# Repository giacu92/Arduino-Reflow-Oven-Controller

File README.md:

# GFE-Reflow-Oven-Controller v2
This repo contains all the files of my Arduino Zero (samd21) based Reflow Oven PID Controller for reflow smd soldering.

* Author: Giacomo Mammarella
* email: giacu92@gmail.com,

[Check the live version!](https://a360.co/3yNSDE0)

# For Arduino Nano (V1.1) refer to appropriate branch --> [v1.1](https://github.com/giacu92/Arduino-Reflow-Oven-Controller/tree/v1.1)

# File list:
* [Arduino files](https://github.com/giacu92/Reflow-Oven-Controller/tree/master/GFE_Reflow_Oven_Controller): The Arduino files source folder.
* [Processing file](https://github.com/giacu92/Reflow-Oven-Controller/tree/master/Processing/Reflow_oven_serial_controller): The Processing files source folder.
* [Prova.brd](https://github.com/giacu92/GFE-Reflow-Oven-Controller/blob/master/Prova.brd): Cadsoft Eagle 6.5 .brd file of my Reflow Oven Controller. 
* [Prova.sch](https://github.com/giacu92/GFE-Reflow-Oven-Controller/blob/master/Prova.sch): Cadsoft Eagle 6.5 .sch file of my Reflow Oven Controller.

# Mounting the board:
Get a fully assembled board [here](http://giacu92.bigcartel.com/product/reflow-oven-controller-board-v1-1) or etch it yourself. -- available soon

A newer version of the pcb featuring two thermocouple interface, +12V fan output (for cooling) is under development. It will fit the 16x2 LCD screen and mounts underneath it. Here's a sample rendering. Also a new pid autotuner function and MicroSD card interface for saving custom profiles are getting implemented.

This project is under continuous update (May 2022). Contact me for anything :)

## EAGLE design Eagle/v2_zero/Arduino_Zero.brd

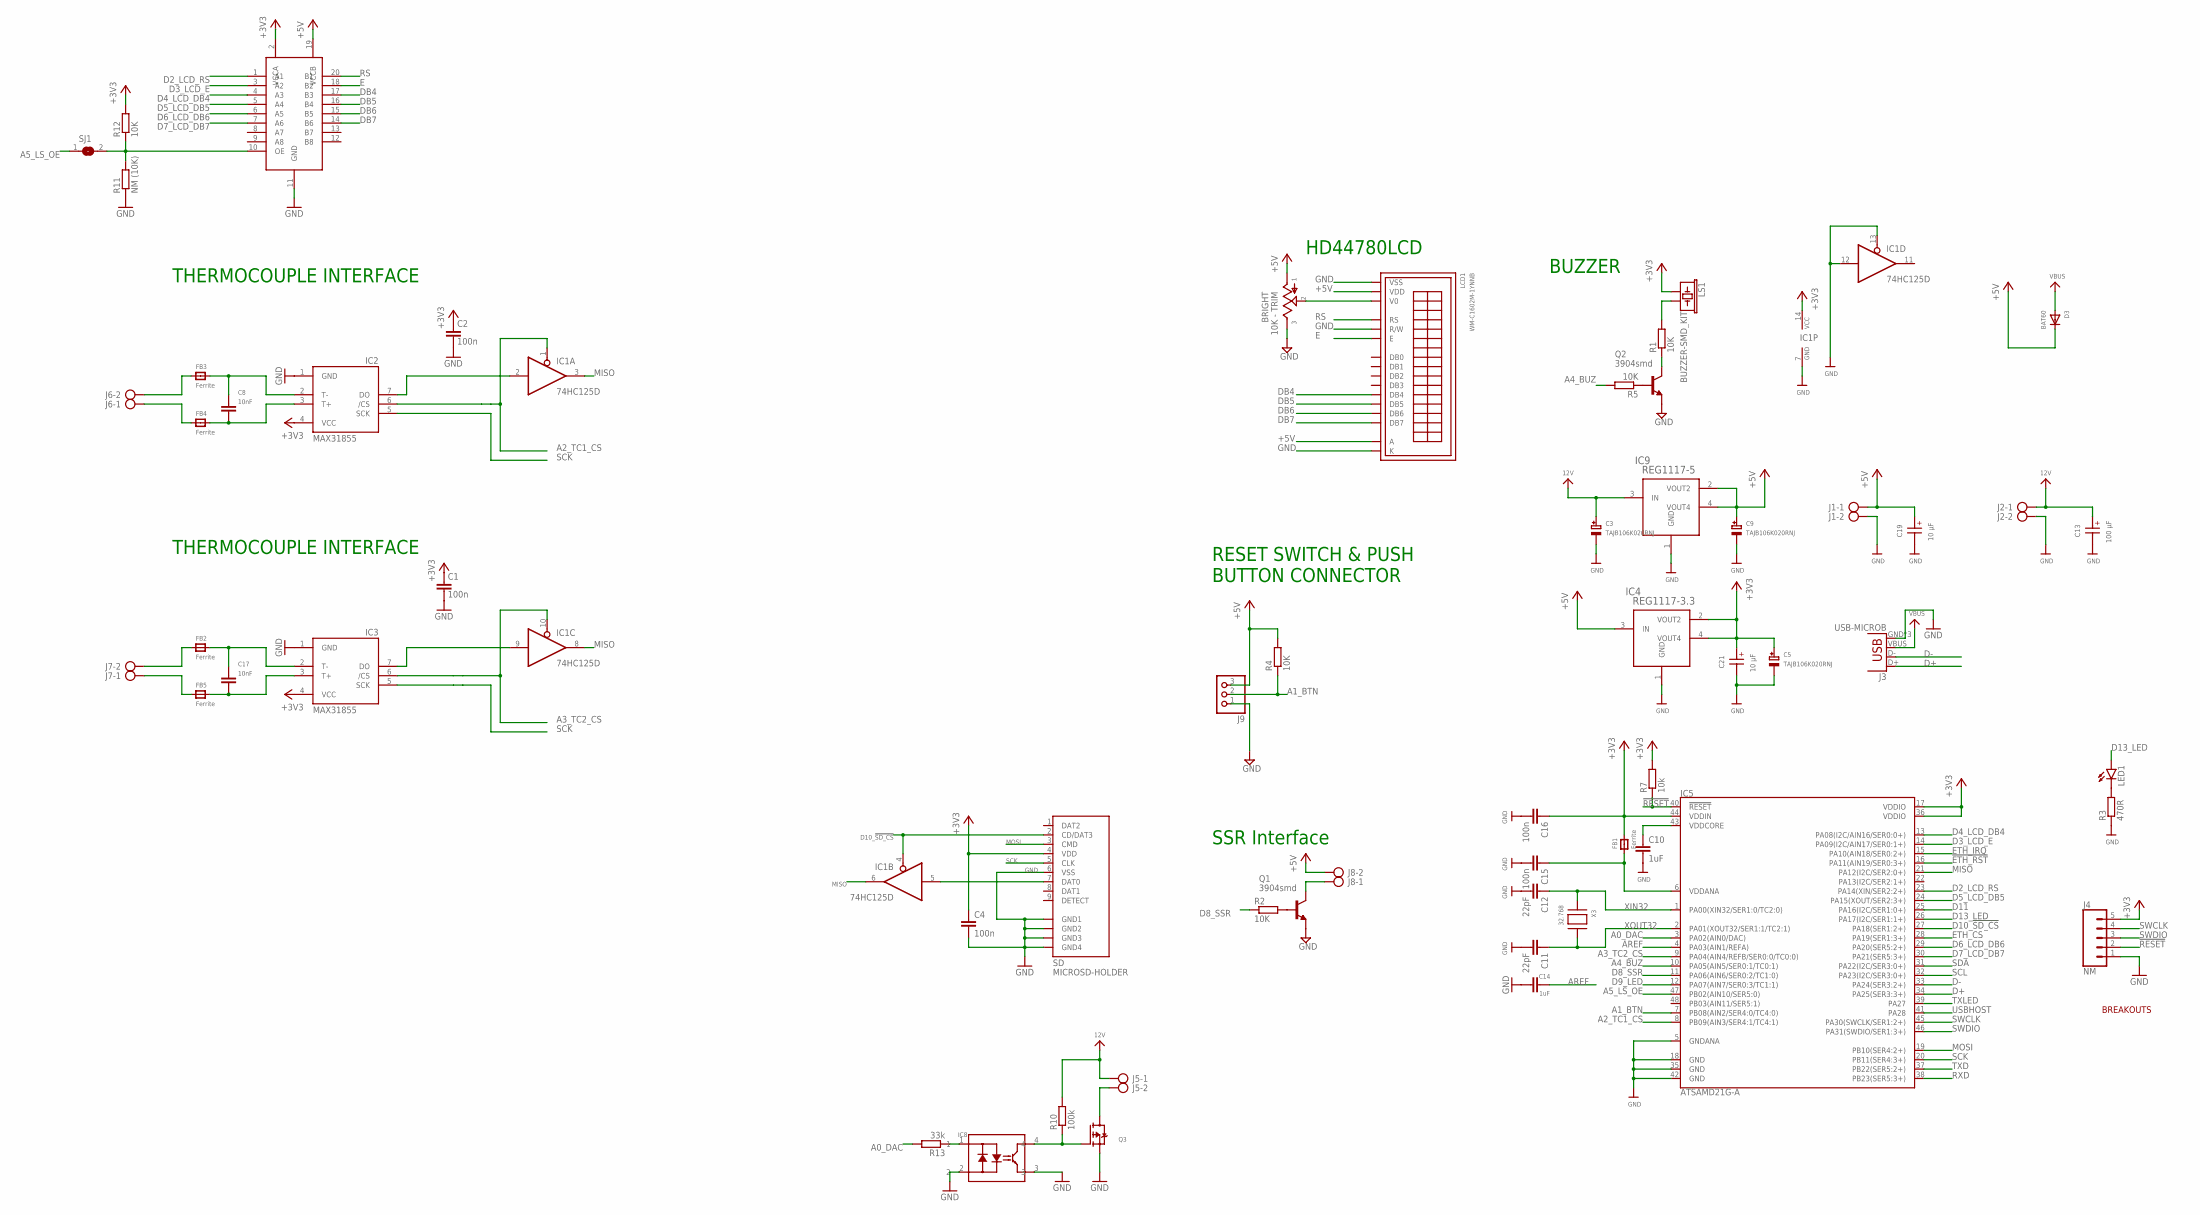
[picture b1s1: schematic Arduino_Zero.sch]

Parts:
BRIGHT: 10K - TRIM; B25P
C1, C2, C4, C15, C16: 100n; C0603K
C3, C5, C9: TAJB106K020RNJ; CAPMP3528X210N
C8, C17: 10nF; C0603K
C10, C14: 1uF; C0603K
C11, C12: 22pF; C0603K
C13: 100 µF; WCAP-ASLI_6.3X7.7(DXL)
C19, C21: 10 µF; WCAP-ASLI_4X5.5(DXL)
D3: BAT60; SOD323
FB1, FB2, FB3, FB4, FB5: Ferrite; BEADC3216X100N
IC1: 74HC125D; SO14
IC2, IC3: MAX31855; SO08
IC4: REG1117-3.3; DCY0004A_N
IC5: ATSAMD21G-A; TQFP-48
IC7: TXS0108E; TSSOP20
IC8: TLP283; SO4_TOS
IC9: REG1117-5; DCY0004A_N
J1, J2, J5, J6, J7, J8: AK500/2ASD; AK500/2
J3: USB-MICROB
J4: NM; 1X05_1.27MM
J9: PINHD-1X3; 1X03
LCD1: WM-C1602M-1YNNB; LCD_2
LED1: LEDCHIPLED_0805; CHIPLED_0805
LS1: BUZZER-SMD_KIT; BUZZER-CCV-KIT
Q1, Q2: 3904smd; SOT23-BEC
Q3: MOSFET-PWIDE; SOT23-WIDE
R1, R2, R4, R5, R12: 10K; R0603
R3: 470R; R0603
R7: 10k; R0603
R10: 100k; R0603
R11: NM (10K); R0603
R13: 33k; R0603
SD: MICROSD-HOLDER; MICROSD-HOLDER-ALIEX
SJ1: SJ
X3: 32.768; XTAL3215

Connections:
12V: C3.1 (+), C13.1 (+), IC9.3 (IN), J2.1, J5.1, R10.2
!ETH_RST: IC5.16 (PA11(AIN19/SER0:3+))
!RESET: IC5.40 (!RESET!), J4.2, R7.1
+3V3: C1.1, C2.1, C4.1, C5.1 (+), C16.1, C21.1 (+), FB1.2, IC1.14 (VCC), IC2.4 (VCC), IC3.4 (VCC), IC4.2 (VOUT2), IC4.4 (VOUT4), IC5.17 (VDDIO), IC5.36 (VDDIO), IC5.44 (VDDIN), IC7.2 (VCCA), J4.5, LS1.+ (1), R7.2, R12.2, SD.4 (VDD)
+5V: BRIGHT.1, C9.1 (+), C19.1 (+), D3.1 (C), IC4.3 (IN), IC7.19 (VCCB), IC9.2 (VOUT2), IC9.4 (VOUT4), J1.1, J8.2, J9.3, LCD1.2 (VDD), LCD1.15 (A), R4.2
A0_DAC: IC5.3 (PA02(AIN0/DAC)), R13.2
A1_BTN: IC5.7 (PB08(AIN2/SER4:0/TC4:0)), J9.2, R4.1
A2_TC1_CS: IC1.1 (OE), IC2.6 (/CS), IC5.8 (PB09(AIN3/SER4:1/TC4:1))
A3_TC2_CS: IC1.10 (OE), IC3.6 (/CS), IC5.9 (PA04(AIN4/REFB/SER0:0/TC0:0))
A4_BUZ: IC5.10 (PA05(AIN5/SER0:1/TC0:1)), R5.2
A5_LS_OE: IC5.47 (PB02(AIN10/SER5:0)), SJ1.1
AREF: C14.1, IC5.4 (PA03(AIN1/REFA))
D2_LCD_RS: IC5.23 (PA14(XIN/SER2:2+)), IC7.1 (A1)
D3_LCD_E: IC5.14 (PA09(I2C/AIN17/SER0:1+)), IC7.3 (A2)
D4_LCD_DB4: IC5.13 (PA08(I2C/AIN16/SER0:0+)), IC7.4 (A3)
D5_LCD_DB5: IC5.24 (PA15(XOUT/SER2:3+)), IC7.5 (A4)
D6_LCD_DB6: IC5.29 (PA20(SER5:2+)), IC7.6 (A5)
D7_LCD_DB7: IC5.30 (PA21(SER5:3+)), IC7.7 (A6)
D8_SSR: IC5.11 (PA06(AIN6/SER0:2/TC1:0)), R2.1
D9_LED: IC5.12 (PA07(AIN7/SER0:3/TC1:1))
D10_!SD_CS: IC1.4 (OE), IC5.27 (PA18(SER1:2+)), SD.2 (CD/DAT3)
D11: IC5.25 (PA16(I2C/SER1:0+))
D13_LED: IC5.26 (PA17(I2C/SER1:1+)), LED1.A
D+: IC5.34 (PA25(SER3:3+)), J3.D+
D-: IC5.33 (PA24(SER3:2+)), J3.D-
DB4: IC7.17 (B3), LCD1.11 (DB4)
DB5: IC7.16 (B4), LCD1.12 (DB5)
DB6: IC7.15 (B5), LCD1.13 (DB6)
DB7: IC7.14 (B6), LCD1.14 (DB7)
E: IC7.18 (B2), LCD1.6 (E)
ETH_CS: IC5.28 (PA19(SER1:3+))
ETH_IRQ: IC5.15 (PA10(AIN18/SER0:2+))
GND: BRIGHT.3, C1.2, C2.2, C3.2 (-), C4.2, C5.2 (-), C9.2 (-), C10.2, C11.2, C12.2, C13.2 (-), C14.2, C15.2, C16.2, C19.2 (-), C21.2 (-), IC1.7 (GND), IC1.12 (I), IC1.13 (OE), IC2.1 (GND), IC3.1 (GND), IC4.1 (GND), IC5.5 (GNDANA), IC5.18 (GND), IC5.35 (GND), IC5.42 (GND), IC7.11 (GND), IC8.2, IC8.3, IC9.1 (GND), J1.2, J2.2, J3.GND, J3.MT1 (GND), J3.MT2 (GND), J4.1, J9.1, LCD1.1 (VSS), LCD1.5 (R/W), LCD1.16 (K), Q1.E, Q2.E, Q3.2 (S), R3.1, R11.1, SD.6 (VSS), SD.P$1 (GND1), SD.P$2 (GND2), SD.P$3 (GND3), SD.P$4 (GND4)
MISO: IC1.3 (O), IC1.6 (O), IC1.8 (O), IC5.21 (PA12(I2C/SER2:0+))
MOSI: IC5.19 (PB10(SER4:2+)), SD.3 (CMD)
unnamed: Q2.B, R5.1
unnamed: J8.1, Q1.C
unnamed: Q1.B, R2.2
unnamed: LS1.- (2), R1.2
unnamed: BRIGHT.2, LCD1.3 (V0)
unnamed: LED1.C, R3.2
unnamed: IC1.2 (I), IC2.7 (DO)
unnamed: IC1.5 (I), SD.7 (DAT0)
unnamed: J5.2, Q3.3 (D)
unnamed: IC7.10 (OE), R11.2, R12.1, SJ1.2
unnamed: FB2.1, J7.2
unnamed: IC8.1, R13.1
unnamed: C17.1, FB2.2, IC3.2 (T-)
unnamed: IC8.4, Q3.1 (G), R10.1
unnamed: FB5.1, J7.1
unnamed: C17.2, FB5.2, IC3.3 (T+)
unnamed: Q2.C, R1.1
unnamed: IC1.9 (I), IC3.7 (DO)
unnamed: FB3.1, J6.2
unnamed: C8.1, FB3.2, IC2.2 (T-)
unnamed: FB4.1, J6.1
unnamed: C8.2, FB4.2, IC2.3 (T+)
unnamed: C15.1, FB1.1, IC5.6 (VDDANA)
unnamed: C10.1, IC5.43 (VDDCORE)
RS: IC7.20 (B1), LCD1.4 (RS)
RXD: IC5.38 (PB23(SER5:3+))
SCK: IC2.5 (SCK), IC3.5 (SCK), IC5.20 (PB11(SER4:3+)), SD.5 (CLK)
SCL: IC5.32 (PA23(I2C/SER3:0+))
SDA: IC5.31 (PA22(I2C/SER3:0+))
SWCLK: IC5.45 (PA30(SWCLK/SER1:2+)), J4.4
SWDIO: IC5.46 (PA31(SWDIO/SER1:3+)), J4.3
TXD: IC5.37 (PB22(SER5:2+))
TXLED: IC5.39 (PA27)
USBHOST: IC5.41 (PA28)
VBUS: D3.2 (A), J3.VBUS
XIN32: C12.1, IC5.1 (PA00(XIN32/SER1:0/TC2:0)), X3.P$1
XOUT32: C11.1, IC5.2 (PA01(XOUT32/SER1:1/TC2:1)), X3.P$2

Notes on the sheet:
SSR Interface
BUZZER
HD44780LCD
RESET SWITCH & PUSH BUTTON CONNECTOR
THERMOCOUPLE INTERFACE
BREAKOUTS

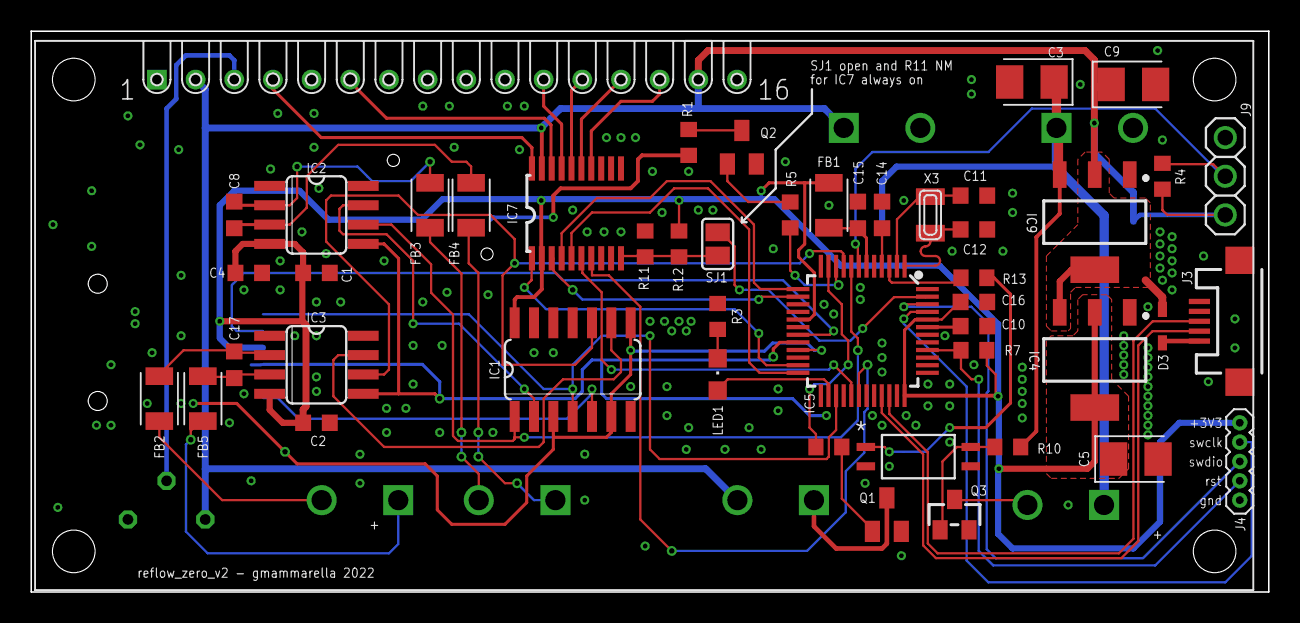
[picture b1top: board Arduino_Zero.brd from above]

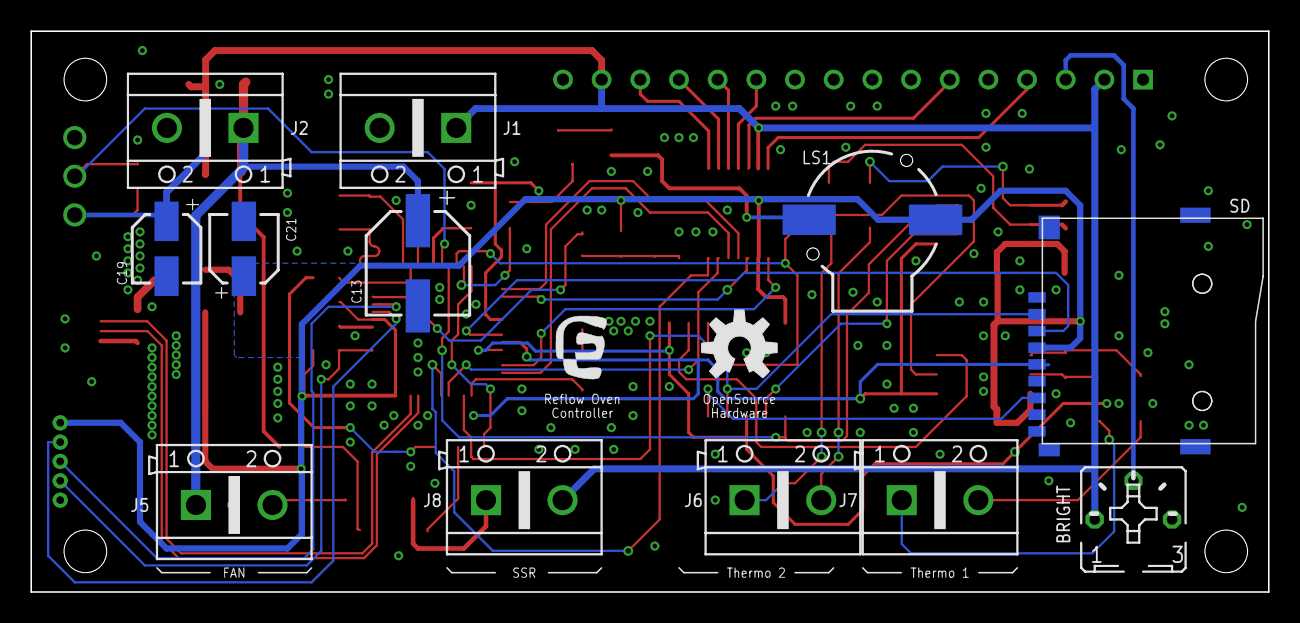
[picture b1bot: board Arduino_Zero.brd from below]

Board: 2 copper layers, 81.3 x 36.8 mm, 62 parts (14 on the bottom side), 61 nets.

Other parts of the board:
U$1: LOGO_PICCOLO
U$2: OSHW-LOGO-M

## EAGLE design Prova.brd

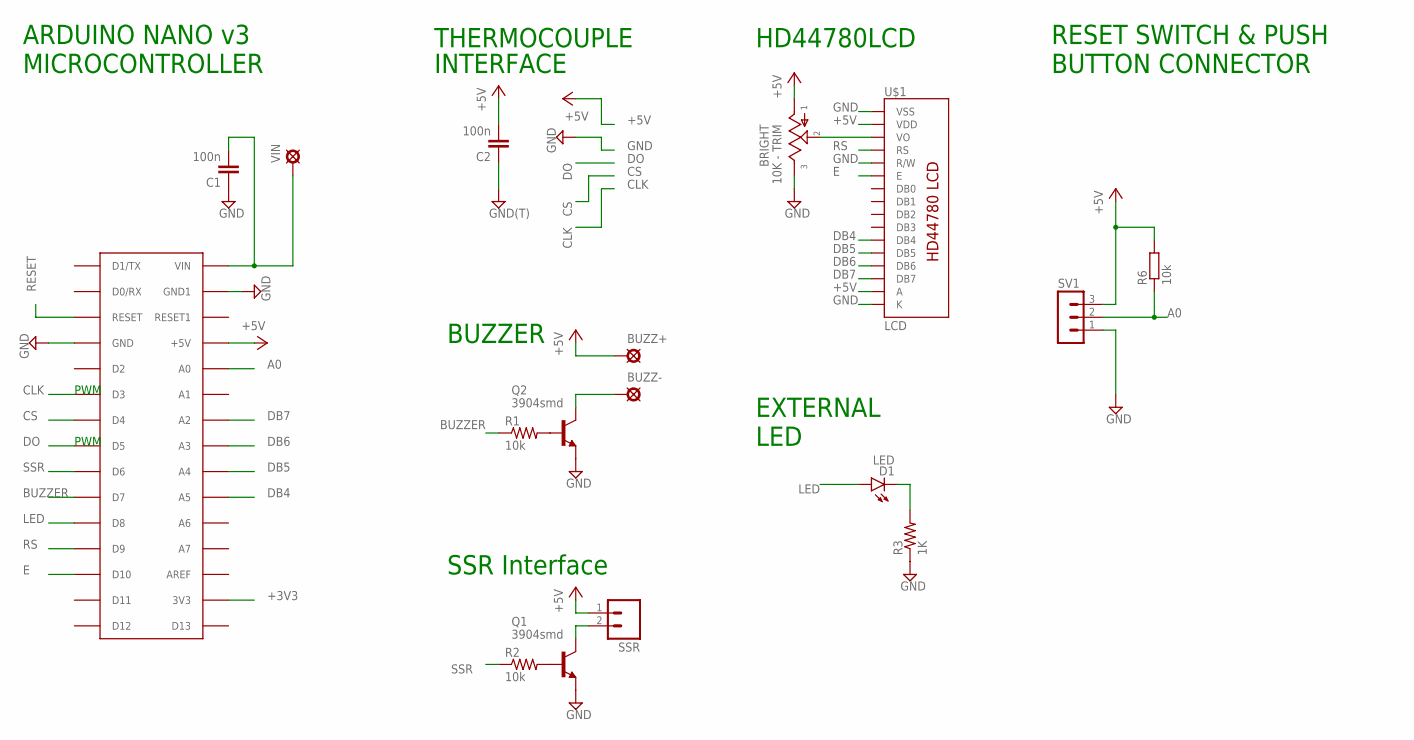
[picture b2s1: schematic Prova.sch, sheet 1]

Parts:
ARDUINO: Arduino Nano v3.0; PDIP-32
BRIGHT: 10K - TRIM; B25P
BUZZ+: PAD; SQUARE
BUZZ-: PAD8; OCTOGON
C1, C2: 100n; 0805
D1: LED; LED3MM
GND8: GND(T); SQUARE
Q1, Q2: 3904smd; SOT23-BEC
R1, R2: 10k; R0207/3
R3: 1K; R0207/3
R6: 10k; M0805
SSR: M023.5MM; SCREWTERMINAL-3.5MM-2
SV1: MA03-1
U$1: LCD; LCD-16X2-PIN
VIN: PAD; SQUARE

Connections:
+3V3: ARDUINO.3V3; also elsewhere on the board
+5V: ARDUINO.+5V, BRIGHT.1, BUZZ+.1, C2.2, R6.2, SSR.1, SV1.3, U$1.2 (VDD), U$1.15 (A)
A0: ARDUINO.A0, R6.1, SV1.2
BUZZER: ARDUINO.D7, R1.1
CLK: ARDUINO.D3; also elsewhere on the board
CS: ARDUINO.D4; also elsewhere on the board
DB4: ARDUINO.A5, U$1.11 (DB4)
DB5: ARDUINO.A4, U$1.12 (DB5)
DB6: ARDUINO.A3, U$1.13 (DB6)
DB7: ARDUINO.A2, U$1.14 (DB7)
DO: ARDUINO.D5; also elsewhere on the board
E: ARDUINO.D10, U$1.6 (E)
GND: ARDUINO.GND, ARDUINO.GND1, BRIGHT.3, C1.1, C2.1, GND8.1, Q1.E, Q2.E, R3.1, SV1.1, U$1.1 (VSS), U$1.5 (R/W), U$1.16 (K); also elsewhere on the board
LED: ARDUINO.D8, D1.A
unnamed: Q2.B, R1.2
unnamed: Q1.C, SSR.2
unnamed: Q1.B, R2.2
unnamed: BUZZ-.1, Q2.C
unnamed: BRIGHT.2, U$1.3 (VO)
unnamed: D1.K (C), R3.2
RESET: ARDUINO.RESET
RS: ARDUINO.D9, U$1.4 (RS)
SSR: ARDUINO.D6, R2.1
VIN: ARDUINO.VIN, C1.2, VIN.1

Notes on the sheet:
SSR Interface
BUZZER
THERMOCOUPLE
INTERFACE
ARDUINO NANO v3 MICROCONTROLLER
HD44780LCD
EXTERNAL LED
RESET SWITCH & PUSH BUTTON CONNECTOR
PWM

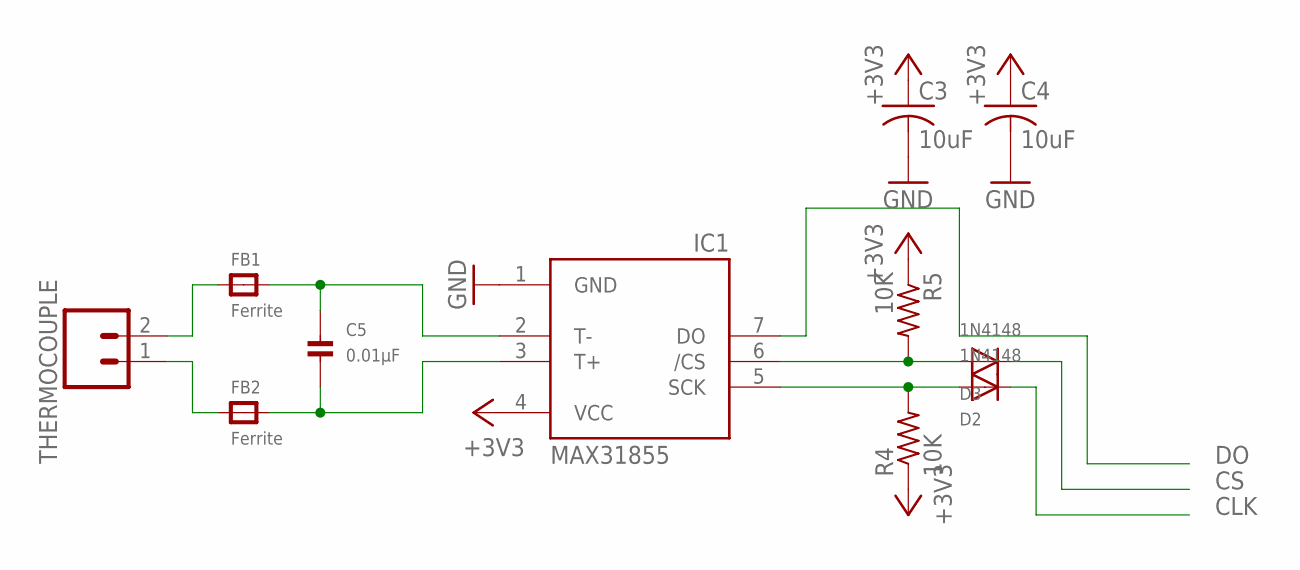
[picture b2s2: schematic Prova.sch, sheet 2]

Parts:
C3, C4: 10uF; C0805K
C5: 0.01µF; _0805
D2, D3: 1N4148; DO-1N4148
FB1, FB2: Ferrite; _0805
IC1: MAX31855; SO08
R4, R5: 10K; R0805
THERMOCOUPLE: M023.5MM; SCREWTERMINAL-3.5MM-2

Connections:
+3V3: C3.1, C4.1, IC1.4 (VCC), R4.1, R5.1; also elsewhere on the board
CLK: D2.C; also elsewhere on the board
CS: D3.C; also elsewhere on the board
CS1: D3.A, IC1.6 (/CS), R5.2
DO: IC1.7 (DO); also elsewhere on the board
GND: C3.2, C4.2, IC1.1 (GND); also elsewhere on the board
unnamed: FB1.1, THERMOCOUPLE.2
unnamed: C5.1, FB1.2, IC1.2 (T-)
unnamed: FB2.1, THERMOCOUPLE.1
unnamed: C5.2, FB2.2, IC1.3 (T+)
SCK: D2.A, IC1.5 (SCK), R4.2

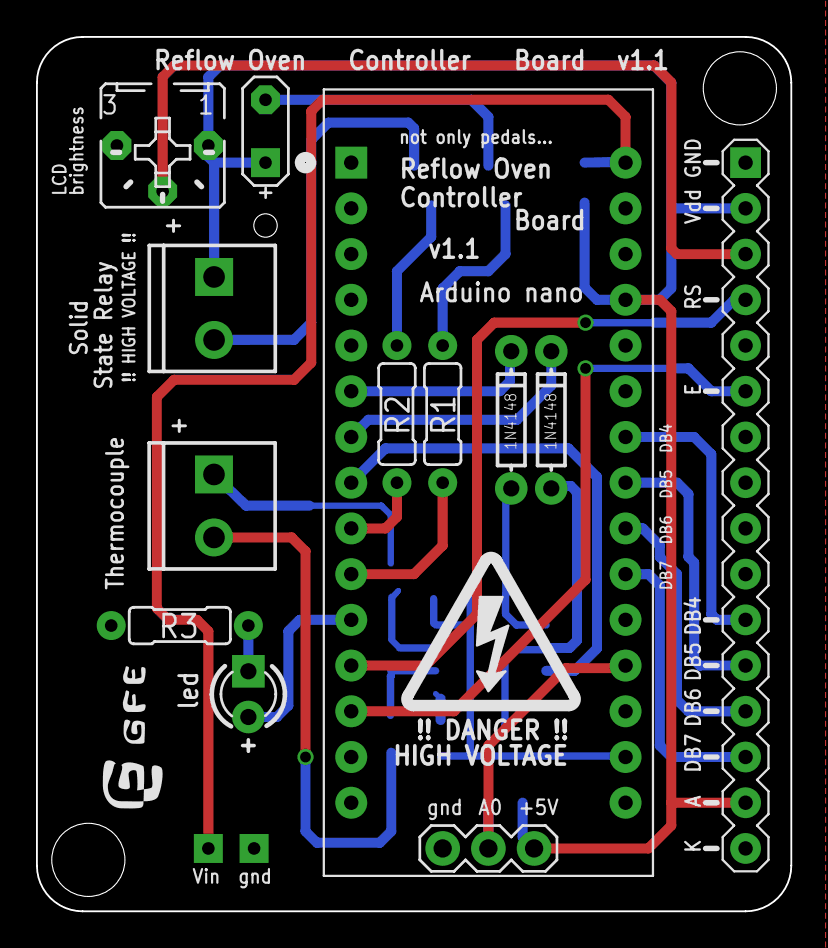
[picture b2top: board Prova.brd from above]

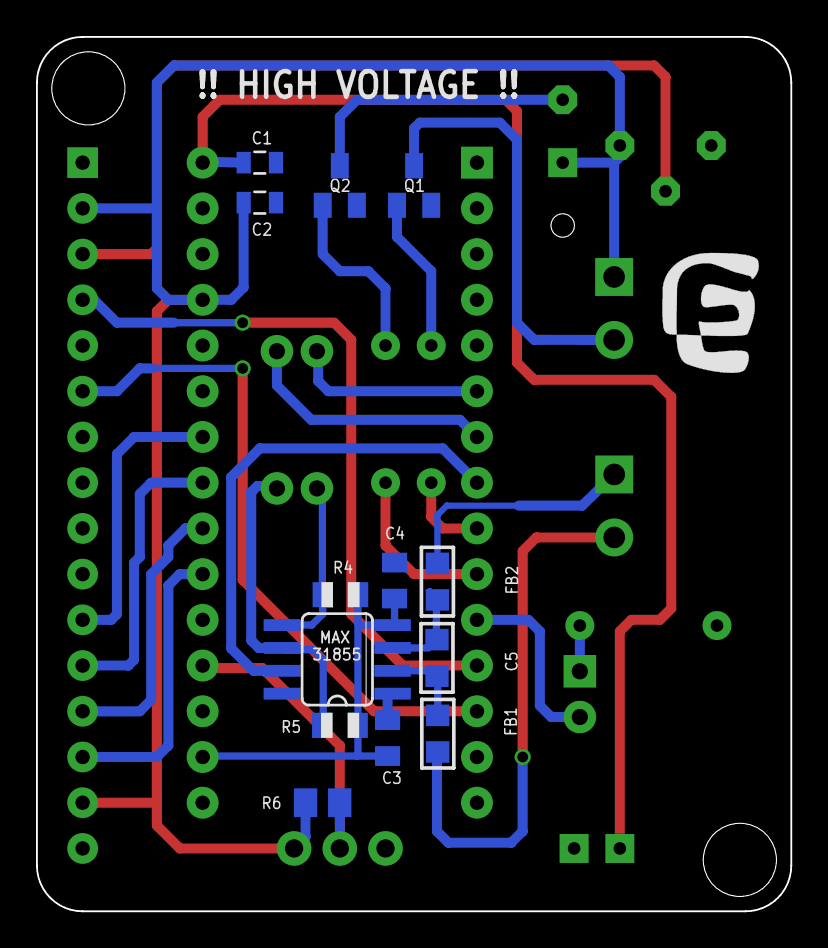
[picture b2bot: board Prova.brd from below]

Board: 2 copper layers, 41.9 x 48.6 mm, 32 parts (14 on the bottom side), 29 nets.

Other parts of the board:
U$2: LOGO_SCRITTA
U$3: RADIOACTIVE_10.00
U$4: LOGO-GRANDE

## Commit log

2016-02-13 Files
    First add of a batch of file for my Arduino Nano SMD Reflow Oven
    Controller
2016-02-14 minor changes
2016-02-15 minor bug fixes
2016-03-23 updates
    updates
2016-03-28 Processing serial GUI
2016-03-28 Building the Processing app
    Added reflow graph
2016-03-29 Arduino sketch
    minor bug fixes
2017-07-04 Now draws temp vs time graph
2017-07-05 Arduino code update and bug fix
2017-07-05 Graphics and communication improvements
2017-08-30 Bug fix on temperatures
2017-08-30 armv6hf application
2018-01-02 bug fix and update
2018-01-02 Graphic update
2018-01-03 update Java serial controller
2018-01-03 Added sounds
2018-01-03 Java Serial controller update
2018-01-03 Added self temperature check
2018-01-04 Added PID autotuner
    PID autotuner still need more adjustments
2018-01-04 Bug fix and macOS application ready
2018-01-04 armv6hf application ready
2018-01-16 Create LICENSE
2018-01-17 Multiplatform executables
2018-01-17 Bug fix
    A stupid commas screwing up it all
2018-01-17 STL file for 3D printed box
2018-02-26 Bug fix
    Fixes a bug when the “profileSet” got hit and didn’t give choice for
    the setting
2018-02-26 update lcd keypad shield
2018-02-26 Lcd keypad shield update
2018-03-11 Bug Fix
    Fixed a bug that may have caused false positive SSR failures check
2018-03-11 Bug Fix
    Fixed a bug that may have caused false positive in SSR power check
2018-11-09 update
    Some mods added like the prior heating, to heat up elements before the cycle starts
2019-12-27 Add Gitpod config
2022-05-11 created v2
    commit
2022-05-11 Create reflow.py
    python serial controller
2022-05-12 update 3d packages
    small updates
2022-05-12 schematic update
2022-05-12 schematic optimization
2022-05-17 v2.0b - ethernet + improvement
    add ethernet support
    Still need to improve SOAK minimum duration
2022-05-19 add eth eagle version
2022-10-06 update on serialController
2022-11-21 added oven simulator and servo pid for cooling
2022-11-21 Added Processing Simulator
2022-11-21 renamed
2022-11-21 new simulator equation
2022-12-03 v2.0b update
2022-12-03 new theme and graphics
2022-12-08 fix ethernet
    Ethernet now working :)
2022-12-13 eth comm
    Ethernet discovery ok.
    Basic ethernet functionality seems ok
2022-12-13 discovery function
2022-12-18 added OTA
2022-12-18 OTA firmware update implemented
2023-01-22 fixes
2023-02-04 small fixes
2023-02-04 openai generated code.. awesome

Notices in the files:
parts and their libraries:
SparkFun-Aesthetics: Licensing: Creative Commons ShareAlike 4.0 International - https://creativecommons.org/licenses/by-sa/4.0
Wurth_Capacitors_WCAP-ASLI: Copyright: Würth Elektronik
COPYRIGHT: Copyright (C) 2022 Ultra Librarian. All rights reserved.
